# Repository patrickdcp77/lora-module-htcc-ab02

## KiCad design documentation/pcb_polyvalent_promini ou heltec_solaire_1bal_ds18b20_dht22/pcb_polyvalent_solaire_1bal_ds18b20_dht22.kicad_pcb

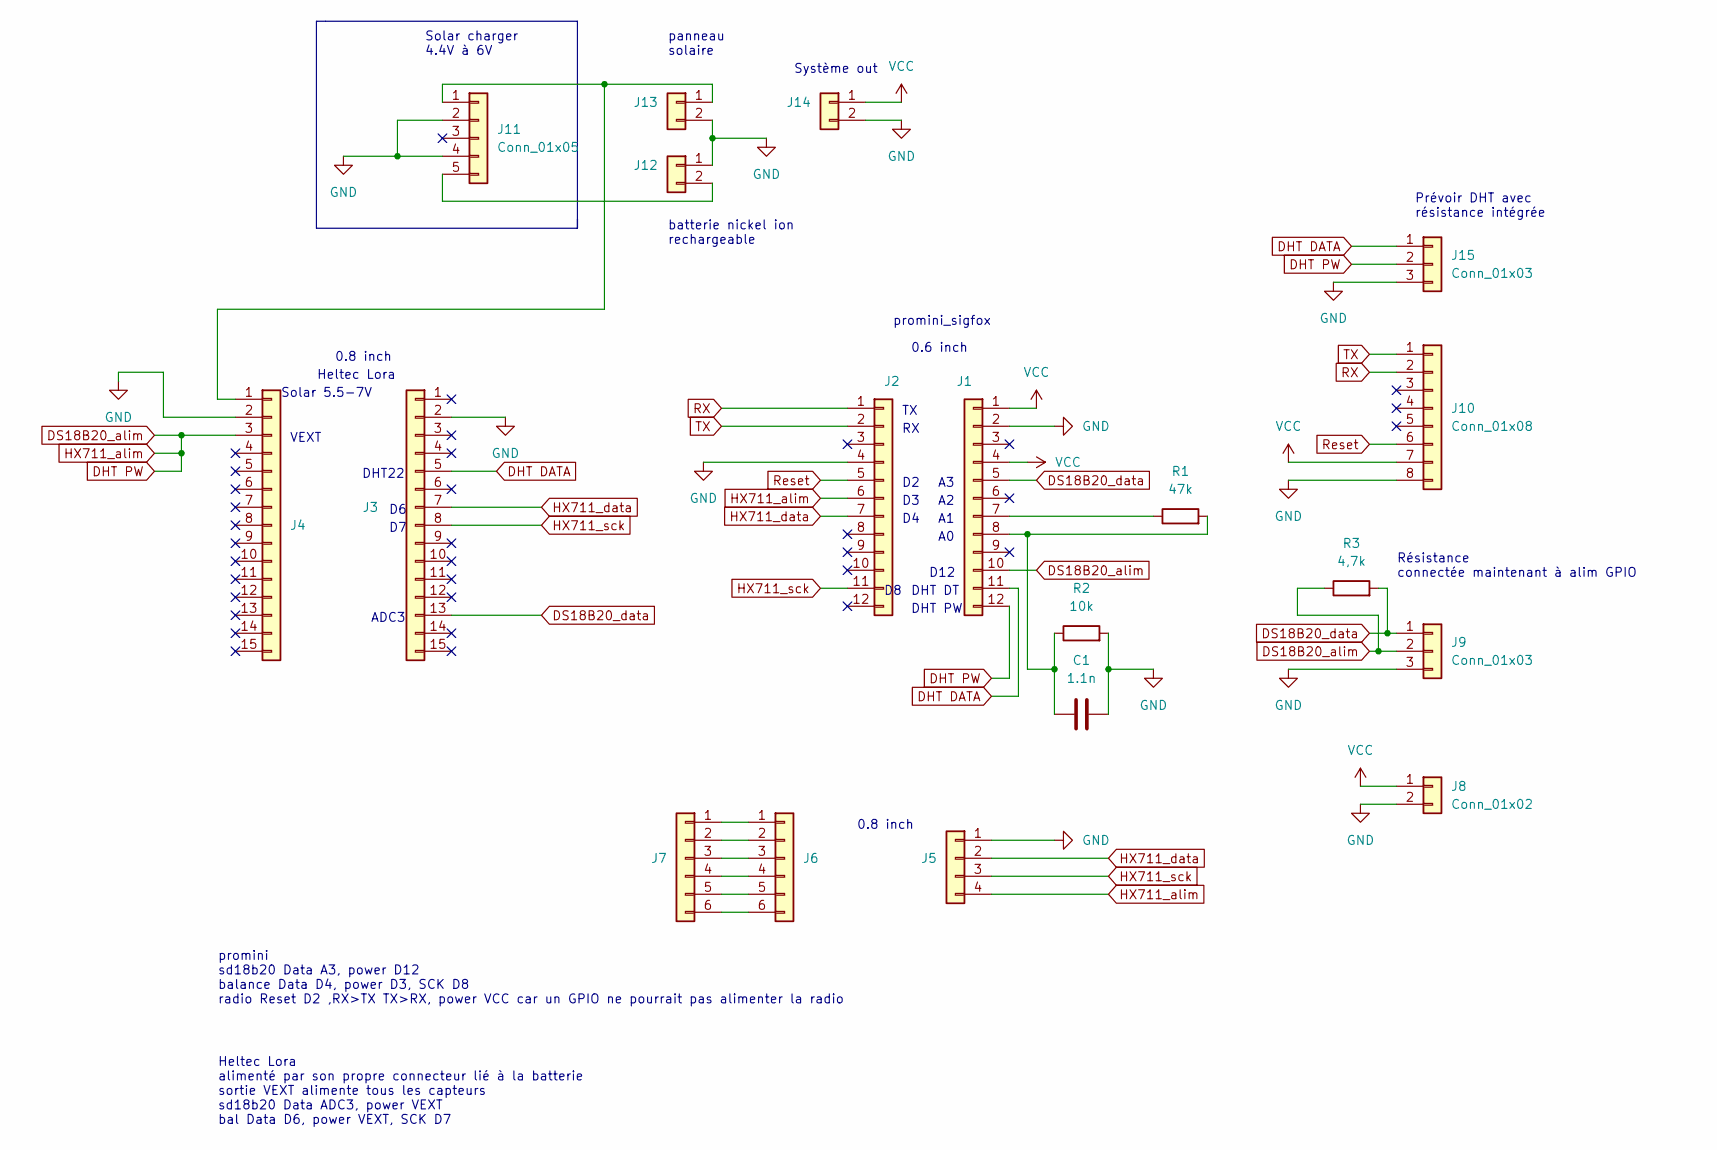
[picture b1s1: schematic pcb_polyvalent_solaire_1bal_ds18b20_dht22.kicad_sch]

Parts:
C1: 1.1n; C_0603_1608Metric_Pad1.08x0.95mm_HandSolder
J1, J2: Conn_01x12; PinSocket_1x12_P2.54mm_Vertical
J3, J4: Conn_01x15; PinSocket_1x15_P2.54mm_Vertical
J5: Conn_01x04; PinSocket_1x04_P2.54mm_Vertical
J6: Conn_01x06; PinSocket_1x06_P2.54mm_Vertical
J7: Conn_01x06; PinHeader_1x06_P2.54mm_Vertical
J8, J12, J13, J14: Conn_01x02; PinHeader_1x02_P2.54mm_Vertical
J9, J15: Conn_01x03; PinHeader_1x03_P2.54mm_Vertical
J10: Conn_01x08; PinSocket_1x08_P2.54mm_Vertical
J11: Conn_01x05; PinSocket_1x05_P2.54mm_Vertical
R1: 47k; R_0603_1608Metric_Pad0.98x0.95mm_HandSolder
R2: 10k; R_0603_1608Metric_Pad0.98x0.95mm_HandSolder
R3: 4,7k; R_0603_1608Metric_Pad0.98x0.95mm_HandSolder

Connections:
DHT DATA: J1.11, J3.5, J15.1
DHT PW: J1.10, J1.12, J2.6, J4.3, J5.4, J9.2, J15.2, R3.1
DS18B20_data: J1.5, J3.13, J9.1, R3.2
GND: C1.2, J1.2, J2.4, J3.2, J4.2, J5.1, J8.2, J9.3, J10.8, J11.2, J11.4, J12.1, J13.2, J14.2, J15.3, R2.2
HX711_data: J2.7, J3.7, J5.2
HX711_sck: J2.11, J3.8, J5.3
unnamed: J1.7, R1.1
unnamed: C1.1, J1.8, R1.2, R2.1
unnamed: J6.1, J7.1
unnamed: J6.2, J7.2
unnamed: J6.3, J7.3
unnamed: J6.4, J7.4
unnamed: J6.5, J7.5
unnamed: J6.6, J7.6
unnamed: J4.1, J11.1, J13.1
unnamed: J11.5, J12.2
RX: J2.1, J10.2
Reset: J2.5, J10.6
TX: J2.2, J10.1
VCC: J1.1, J1.4, J8.1, J10.7, J14.1

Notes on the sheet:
Solar charger 4.4V à 6V
Système out
Solar 5.5-7V
DHT DT
0.8 inch
Résistance connectée maintenant à alim GPIO
DHT22
Heltec Lora alimenté par son propre connecteur lié à la batterie sortie VEXT alimente tous les capteurs sd18b20 Data ADC3, power VEXT bal Data D6, power VEXT, SCK D7
Heltec Lora
DHT PW
promini_sigfox
ADC3
VEXT
D12
0.6 inch
batterie nickel ion rechargeable
Prévoir DHT avec résistance intégrée
panneau solaire
promini sd18b20 Data A3, power D12 balance Data D4, power D3, SCK D8 radio Reset D2 ,RX>TX TX>RX, power VCC car un GPIO ne pourrait pas alimenter la radio

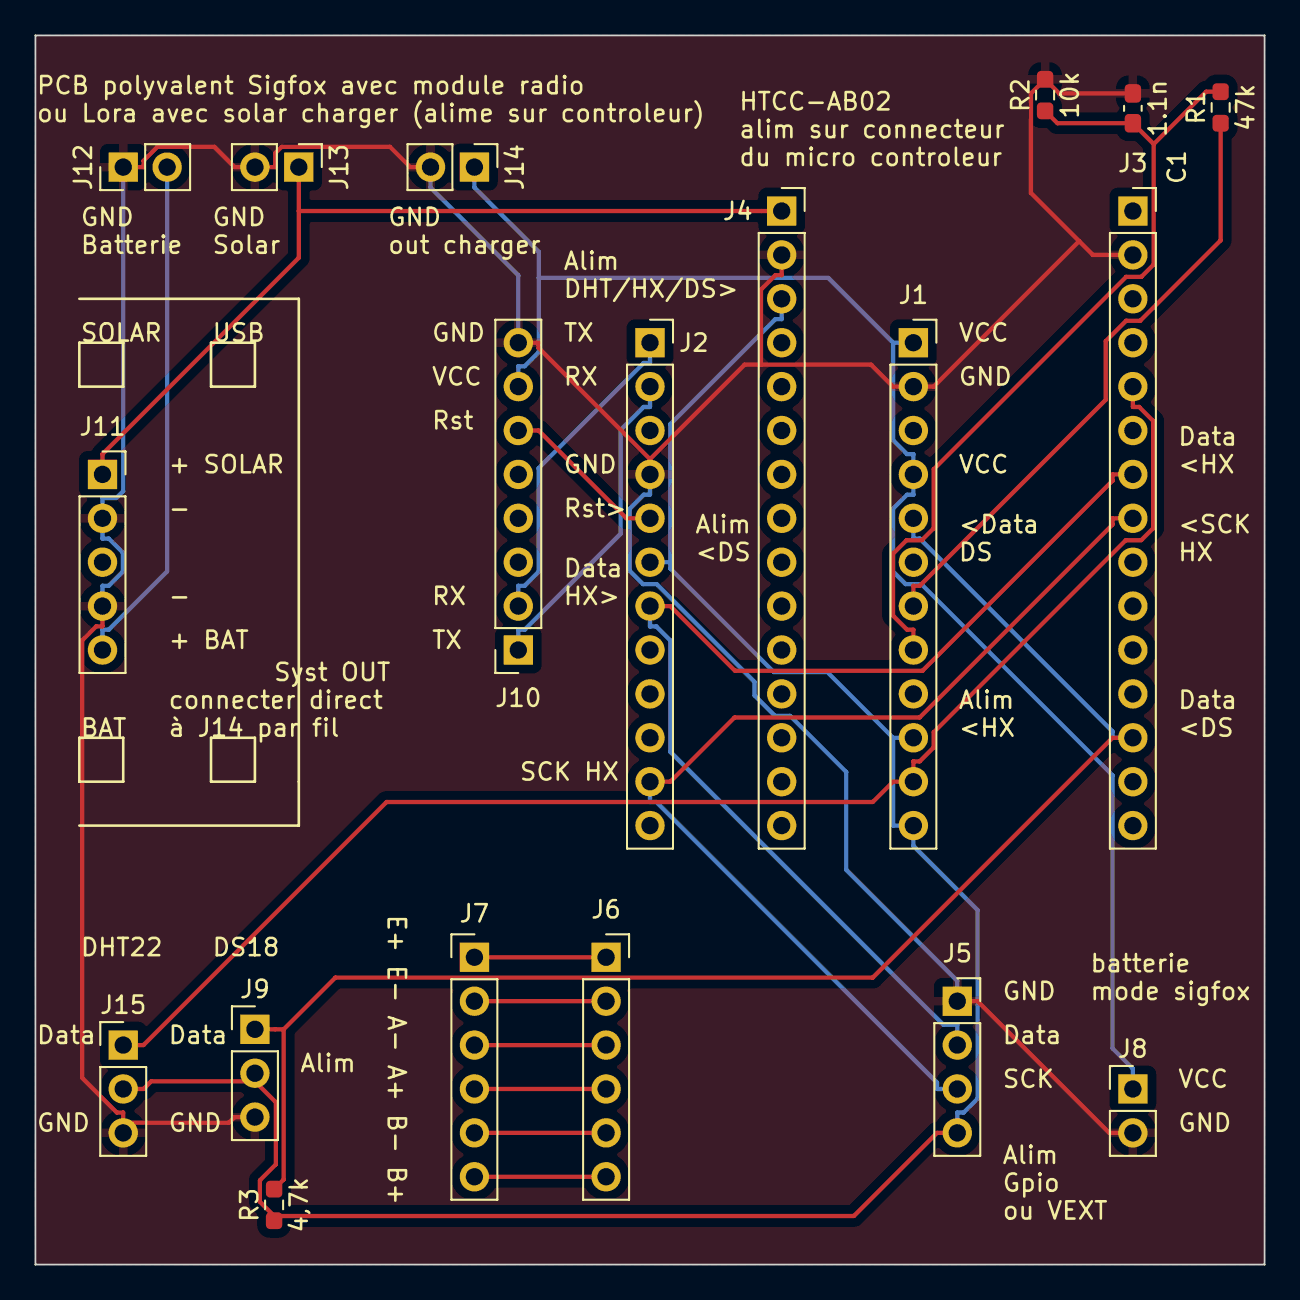
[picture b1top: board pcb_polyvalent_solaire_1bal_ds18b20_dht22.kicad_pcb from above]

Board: 2 copper layers, 71.1 x 71.1 mm, 19 parts (0 on the bottom side), 20 nets.

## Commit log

2023-07-28 projet fonctionnant déjà
2023-07-28 encore un essai
2023-07-28 dernier pour essai push
2023-07-28 soft vérifié avec la boite lora-10
2024-09-22 mise à jour pour lora-01
2024-09-22 mise à jour lora-01
2024-09-22 mise à jour lora-01 avec la sonde seule et soft GPT
2024-09-22 delais d'envoi 1mn
2024-09-22 essais changementspull et push réussits
2024-09-22 ajout d'une documentation sur le projet
2024-09-22 ajout d'une documentation sur la fabrication du PCB polyvalent sigfox lora
2024-09-22 changement commentaire dans schéma
2024-09-22 change dossier kicad en version 8
2024-09-22 ajout vue 3D PCB
2024-09-23 intègre if debugg
2024-09-23 MAJ supprime dossier en trop
2024-11-16 essai
2024-11-16 essai01
